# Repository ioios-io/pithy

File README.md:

# The Pithy Range @ [ioios.io](https://ioios.io/products/pithy)

---
## The quickest way to add extra control to your Smart Home
 The Pithy range was conceived to fill the gap in the smart home arena so as to provide simple and intuitive phyiscal controls for adjusting volume, dimming lights, changing heating settings or whatever you chose!

The Open-Source devices are centered around a Wemos D1 Mini and they all feature a rotary encoder, a side switch and a temperature/huimdity sensor. Additionally, the Pixel model has a 16 LED NeoPixel ring for a display whilst the Screen model has... you guessed it, a screen.

## Pins
When writing esphome configuration for the Pithy range you will need to use the following pins for the latest board versions.

| Function         | D1 Mini PIN |
|------------------|-------------|
| I2C Clock        | D3          |
| I2C Data         | D4          |
| Side Button      | TX          |
| PIR Sensor 1*    | D1          |
| PIR Sensor 2*    | D2          |
| Rotary Encoder A | D5          |
| Rotary Encoder B | D6          |
| Rotary Switch    | D7          |
| NeoPixels*       | RX          |
| DHT22 Temp*      | D0          |

(* Denotes items that may not be installed on all versions of a given model)

## The Files
In this repo you will find both the PCB files and the cases. In both sections the files are provided in multiple formats and include the official designs and also community contributions.
##### The Design Process
The PCBs were designed in Autodesk Eagle (using a custom made component library with 100% 3D renders). They were then imported/linked to Autodesk Fusion 360 where the cases were designed to perfectly fit and compliemnt the PCBs.

## Contributions
It is Open-Source for a reason! If you would like to contribute your modifications or creations to the project, please follow these steps:
1. Fork this repo
2. Create a new, descriptively-named directory within the appropriate 'community' directory
3. Create a README.md file to briefly explain your ideas and if required, instructions for use/assembly
4. Don't forget to credit yourself and anyone else involved!
4. Create a pull request

___

```
John Lumley
15th March 2021
```

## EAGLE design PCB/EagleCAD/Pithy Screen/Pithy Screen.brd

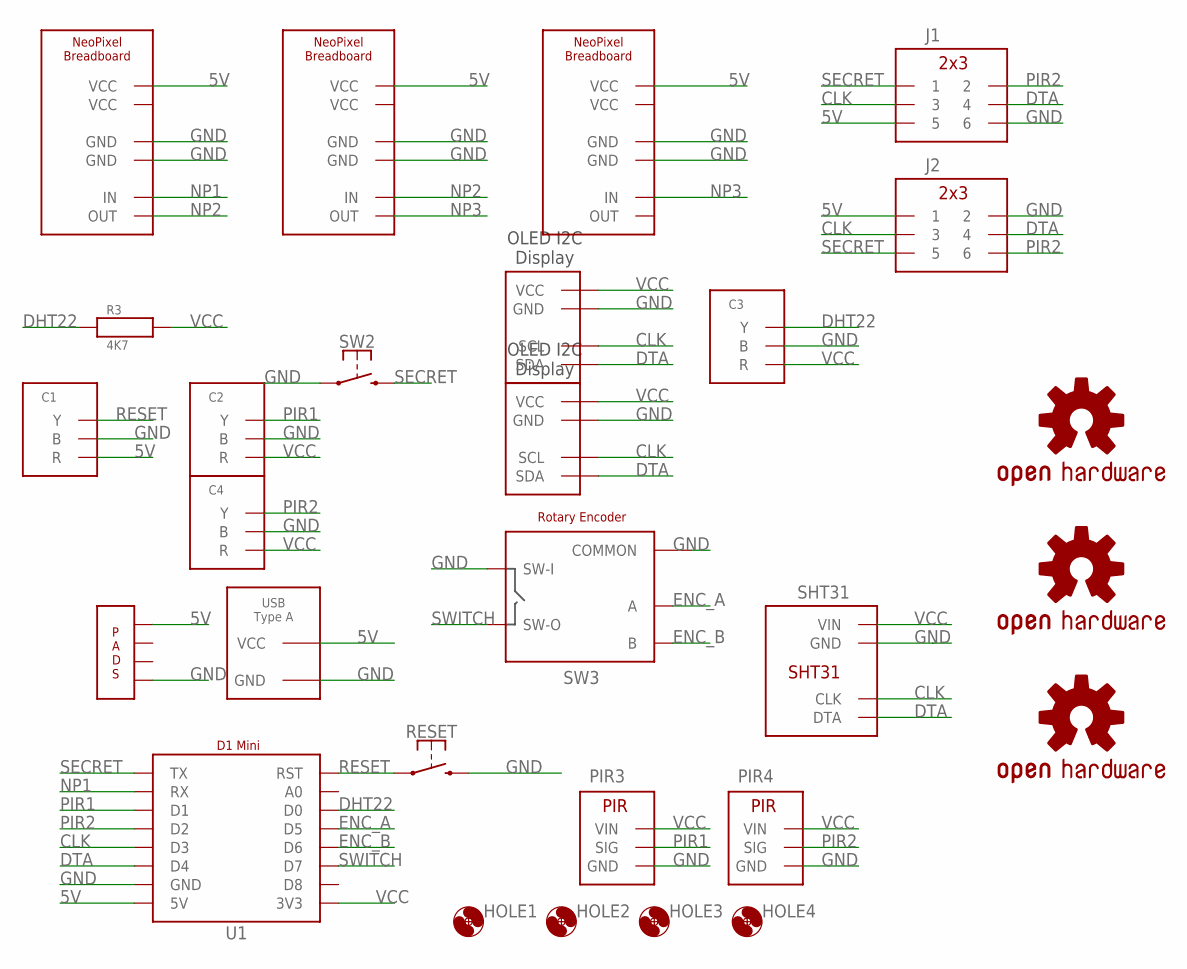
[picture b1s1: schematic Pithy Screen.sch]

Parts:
C1, C2, C3, C4: JST_2MM_3PIN
HOLE1, HOLE2, HOLE3, HOLE4: HOLE_3.2
J1, J2: DIL_2X03FEMALE; 2X3-RAF
LOGO1: OSHW-LOGOL; OSHW-LOGO-L
LOGO2: OSHW-LOGOM; OSHW-LOGO-M
LOGO3: OSHW-LOGOS; OSHW-LOGO-S
NP1, NP2, NP3: NEOPIXEL_BREADBOARD
PIR3, PIR4: PIR45DEG; PIR_45DEG
R3: 4K7; 1/4W_RESISTOR
RESET: SPDT_MOMENTARY; SPDT_RIGHT_ANGLE
SHT31: SHT31RIGHT_ANGLED; SHT31_RIGHT_ANGLE
SW2: SPDT_MOMENTARY; SPDT_RIGHT_ANGLE
SW3: ENCODER; ROTARY_ENCODER
U1: D1_MINI
U2, U3: OLED_I2C_0.9"VCC_LEFT; OLED_I2C_0.9"_ALT
U$1: USB_TYPE_A; USB_TYPE_A_BACKWARDS
U$2: PADS_4

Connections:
5V: C1.RED (R), J1.5, J2.1, NP1.VCC, NP2.VCC, NP3.VCC, U1.5V, U$1.VCC, U$2.P$4
CLK: J1.3, J2.3, SHT31.CLK, U1.D3, U2.SCL, U3.SCL
DHT22: C3.YELLOW (Y), R3.P$1, U1.D0
DTA: J1.4, J2.4, SHT31.DTA, U1.D4, U2.SDA, U3.SDA
ENC_A: SW3.A, U1.D5
ENC_B: SW3.B, U1.D6
GND: C1.BLACK (B), C2.BLACK (B), C3.BLACK (B), C4.BLACK (B), J1.6, J2.2, NP1.GND, NP1.GND@2 (GND), NP2.GND, NP2.GND@2 (GND), NP3.GND, NP3.GND@2 (GND), PIR3.GND, PIR4.GND, RESET.2 (3), SHT31.GND, SW2.1, SW3.C (COMMON), SW3.SW+ (SW-I), U1.GND, U2.GND, U3.GND, U$1.GND, U$2.P$1
NP1: NP1.IN, U1.RX
NP2: NP1.OUT, NP2.IN
NP3: NP2.OUT, NP3.IN
PIR1: C2.YELLOW (Y), PIR3.SIG, U1.D1
PIR2: C4.YELLOW (Y), J1.2, J2.6, PIR4.SIG, U1.D2
RESET: C1.YELLOW (Y), RESET.1, U1.RST
SECRET: J1.1, J2.5, SW2.2 (3), U1.TX
SWITCH: SW3.SW- (SW-O), U1.D7
VCC: C2.RED (R), C3.RED (R), C4.RED (R), PIR3.VCC (VIN), PIR4.VCC (VIN), R3.P$2, SHT31.VIN, U1.3V3, U2.VCC, U3.VCC

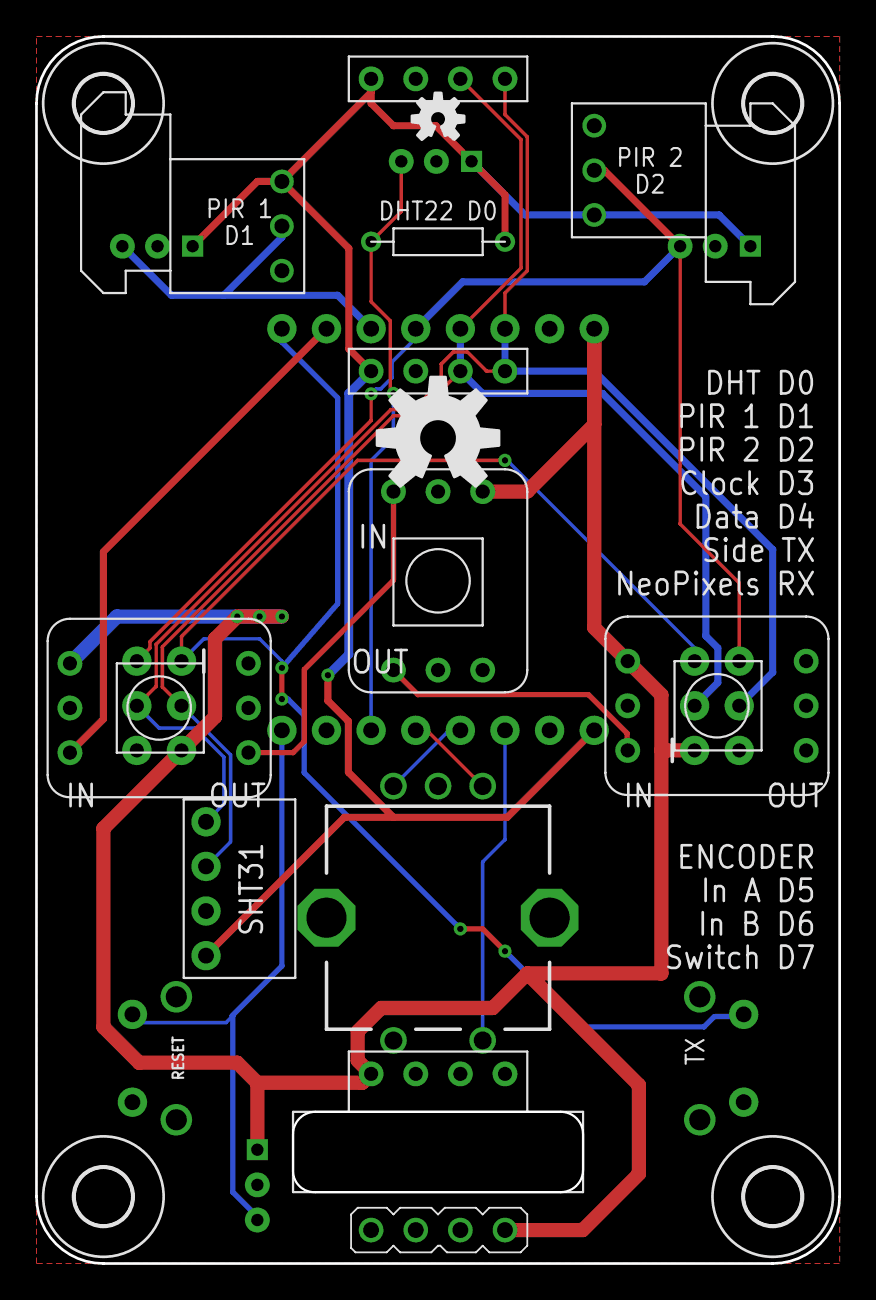
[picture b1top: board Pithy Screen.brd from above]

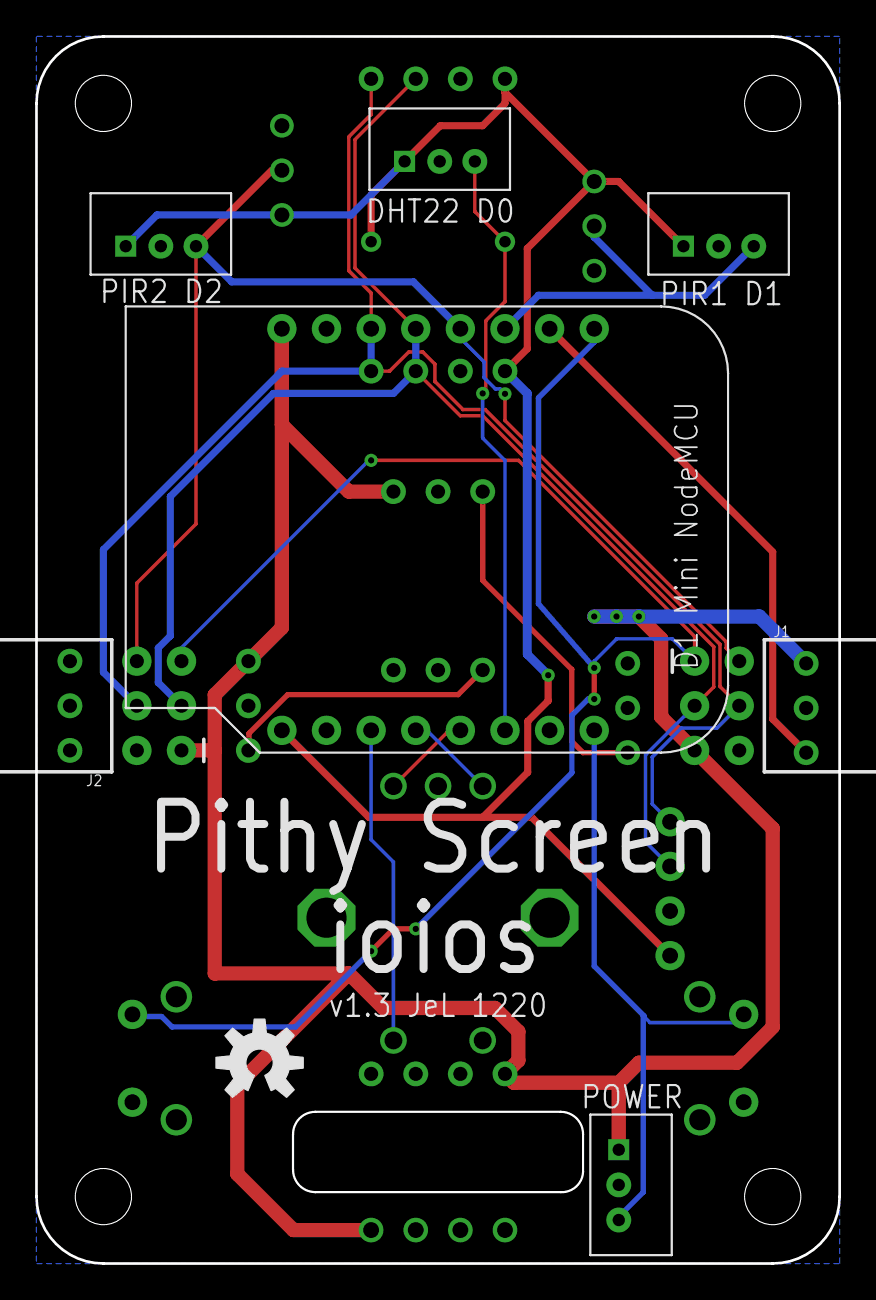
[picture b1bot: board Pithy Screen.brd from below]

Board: 2 copper layers, 45.7 x 69.8 mm, 28 parts (8 on the bottom side), 16 nets.

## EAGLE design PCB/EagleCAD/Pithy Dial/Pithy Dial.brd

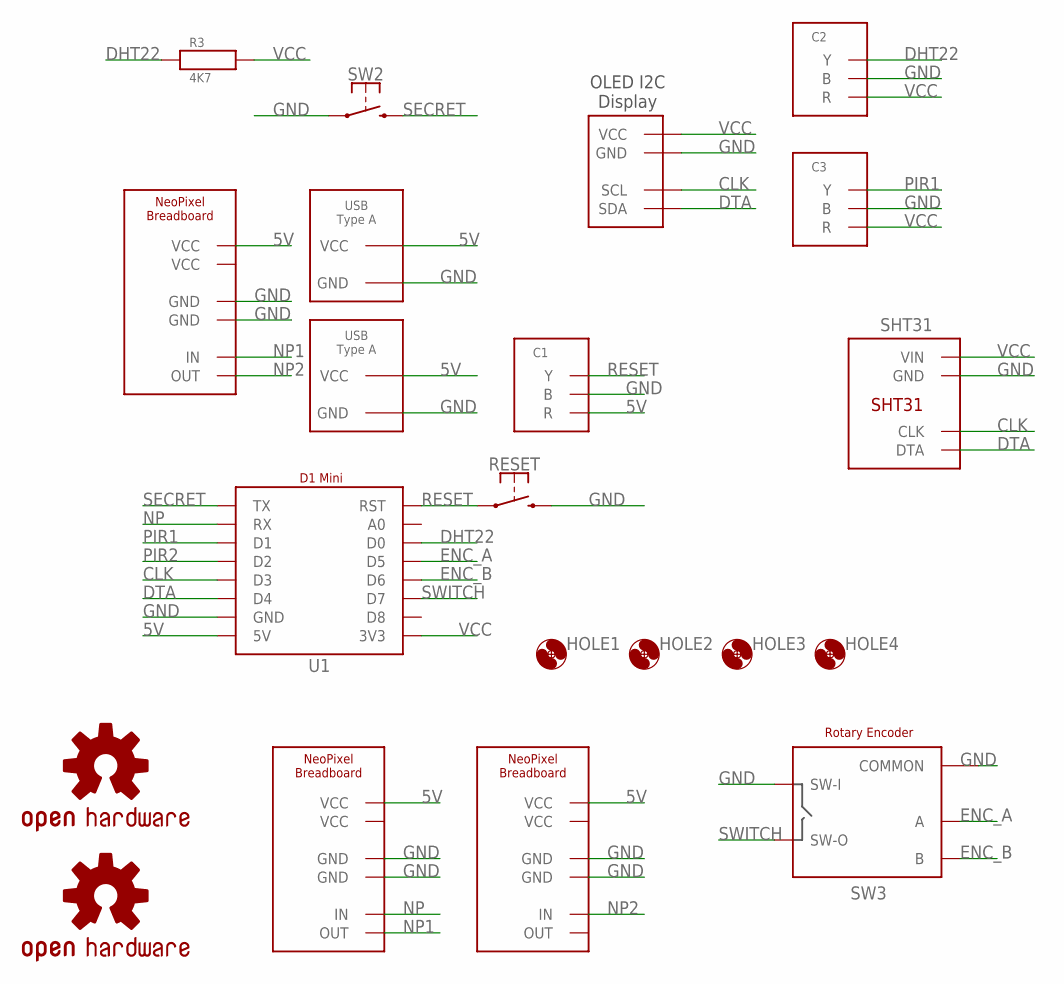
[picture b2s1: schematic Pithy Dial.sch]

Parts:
C1, C2, C3: JST_2MM_3PIN
HOLE1, HOLE2, HOLE3, HOLE4: HOLE_3.2
LOGO1: OSHW-LOGOM; OSHW-LOGO-M
LOGO2: OSHW-LOGOS; OSHW-LOGO-S
NP1: NEOPIXEL_BREADBOARD
NP2: LEFT_NEOPIXEL; NEOPIXEL_BREADBOARD
NP3: RIGHT_NEOPIXEL; NEOPIXEL_BREADBOARD
R3: 4K7; 1/4W_RESISTOR
RESET: SPDT_MOMENTARY; SPDT_RIGHT_ANGLE
SHT31: SHT31RIGHT_ANGLED; SHT31_RIGHT_ANGLE
SW2: SPDT_MOMENTARY; SPDT_RIGHT_ANGLE
SW3: ENCODER; ROTARY_ENCODER
U1: D1_MINI
U2: OLED_I2C_0.9"VCC_LEFT; OLED_I2C_0.9"_ALT
U$1, U$3: USB_TYPE_A; USB_TYPE_A_BACKWARDS

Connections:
5V: C1.RED (R), NP1.VCC, NP2.VCC, NP3.VCC, U1.5V, U$1.VCC, U$3.VCC
CLK: SHT31.CLK, U1.D3, U2.SCL
DHT22: C2.YELLOW (Y), R3.P$1, U1.D0
DTA: SHT31.DTA, U1.D4, U2.SDA
ENC_A: SW3.A, U1.D5
ENC_B: SW3.B, U1.D6
GND: C1.BLACK (B), C2.BLACK (B), C3.BLACK (B), NP1.GND, NP1.GND@2 (GND), NP2.GND, NP2.GND@2 (GND), NP3.GND, NP3.GND@2 (GND), RESET.2 (3), SHT31.GND, SW2.1, SW3.C (COMMON), SW3.SW+ (SW-I), U1.GND, U2.GND, U$1.GND, U$3.GND
NP: NP2.IN, U1.RX
NP1: NP1.IN, NP2.OUT
NP2: NP1.OUT, NP3.IN
PIR1: C3.YELLOW (Y), U1.D1
PIR2: U1.D2
RESET: C1.YELLOW (Y), RESET.1, U1.RST
SECRET: SW2.2 (3), U1.TX
SWITCH: SW3.SW- (SW-O), U1.D7
VCC: C2.RED (R), C3.RED (R), R3.P$2, SHT31.VIN, U1.3V3, U2.VCC

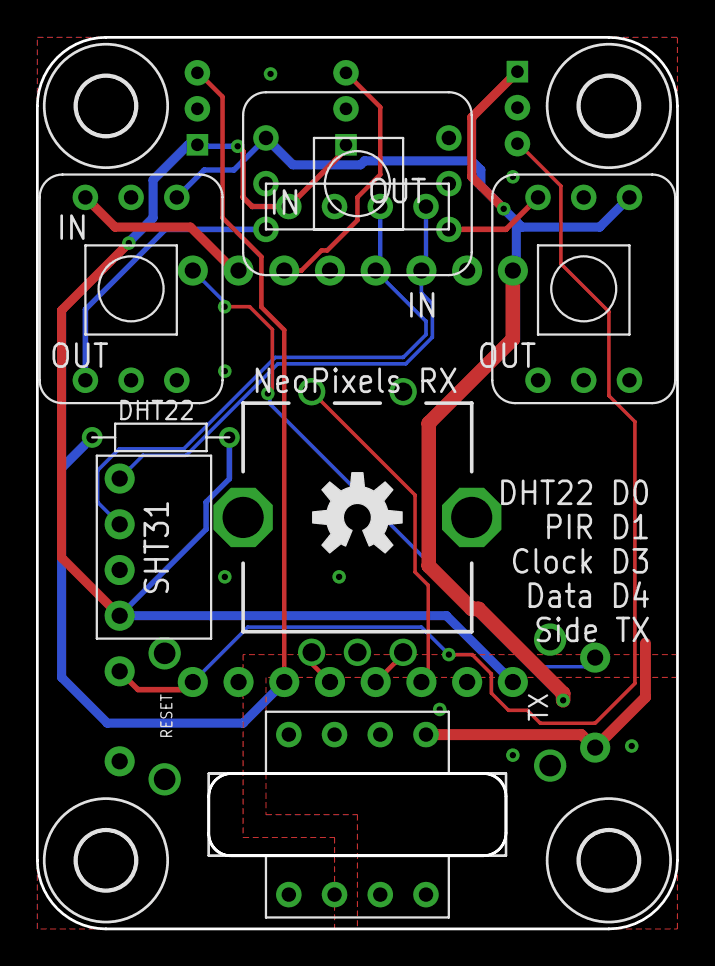
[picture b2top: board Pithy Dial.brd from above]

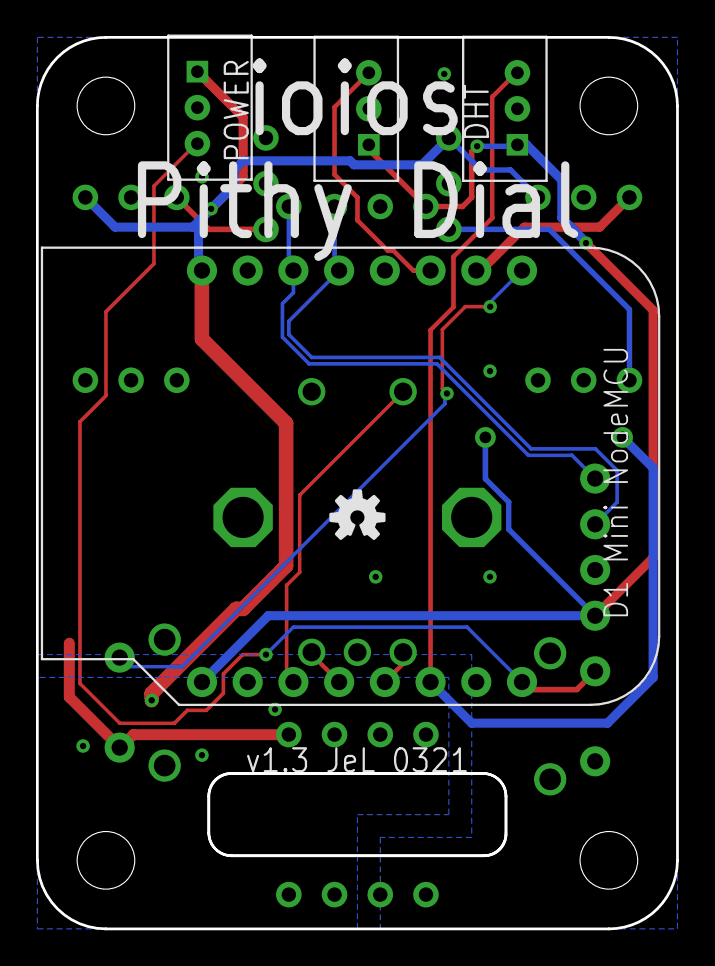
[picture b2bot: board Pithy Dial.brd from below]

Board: 2 copper layers, 35.6 x 49.5 mm, 21 parts (5 on the bottom side), 15 nets.

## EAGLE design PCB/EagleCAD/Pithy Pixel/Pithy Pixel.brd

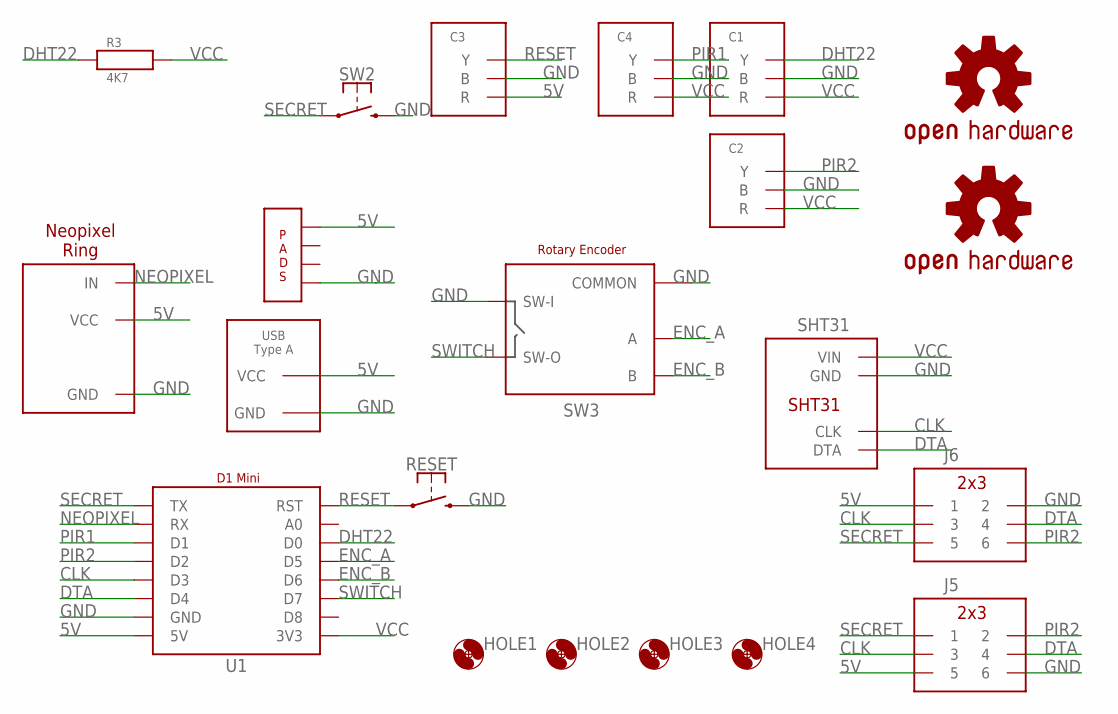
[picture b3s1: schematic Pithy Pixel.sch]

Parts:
C1, C2, C3, C4: JST_2MM_3PIN
HOLE1, HOLE2, HOLE3, HOLE4: HOLE_3.2
IC1: NEOPIXEL_RING_NO_OUT; NEOPIXEL_RING_SMALL_NO_OUT
J5, J6: DIL_2X03FEMALE; 2X3-RAF
LOGO1: OSHW-LOGOM; OSHW-LOGO-M
LOGO2: OSHW-LOGOS; OSHW-LOGO-S
R3: 4K7; 1/4W_RESISTOR
RESET: SPDT_MOMENTARY; SPDT_RIGHT_ANGLE
SHT31: SHT31RIGHT_ANGLED; SHT31_RIGHT_ANGLE
SW2: SPDT_MOMENTARY; SPDT_RIGHT_ANGLE
SW3: ENCODER; ROTARY_ENCODER
U1: D1_MINI
U$1: USB_TYPE_A; USB_TYPE_A_BACKWARDS
U$2: PADS_4

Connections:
5V: C3.RED (R), IC1.VCC@1 (VCC), J5.5, J6.1, U1.5V, U$1.VCC, U$2.P$4
CLK: J5.3, J6.3, SHT31.CLK, U1.D3
DHT22: C1.YELLOW (Y), R3.P$1, U1.D0
DTA: J5.4, J6.4, SHT31.DTA, U1.D4
ENC_A: SW3.A, U1.D5
ENC_B: SW3.B, U1.D6
GND: C1.BLACK (B), C2.BLACK (B), C3.BLACK (B), C4.BLACK (B), IC1.GND@2 (GND), J5.6, J6.2, RESET.2 (3), SHT31.GND, SW2.2 (3), SW3.C (COMMON), SW3.SW+ (SW-I), U1.GND, U$1.GND, U$2.P$1
NEOPIXEL: IC1.IN, U1.RX
PIR1: C4.YELLOW (Y), U1.D1
PIR2: C2.YELLOW (Y), J5.2, J6.6, U1.D2
RESET: C3.YELLOW (Y), RESET.1, U1.RST
SECRET: J5.1, J6.5, SW2.1, U1.TX
SWITCH: SW3.SW- (SW-O), U1.D7
VCC: C1.RED (R), C2.RED (R), C4.RED (R), R3.P$2, SHT31.VIN, U1.3V3

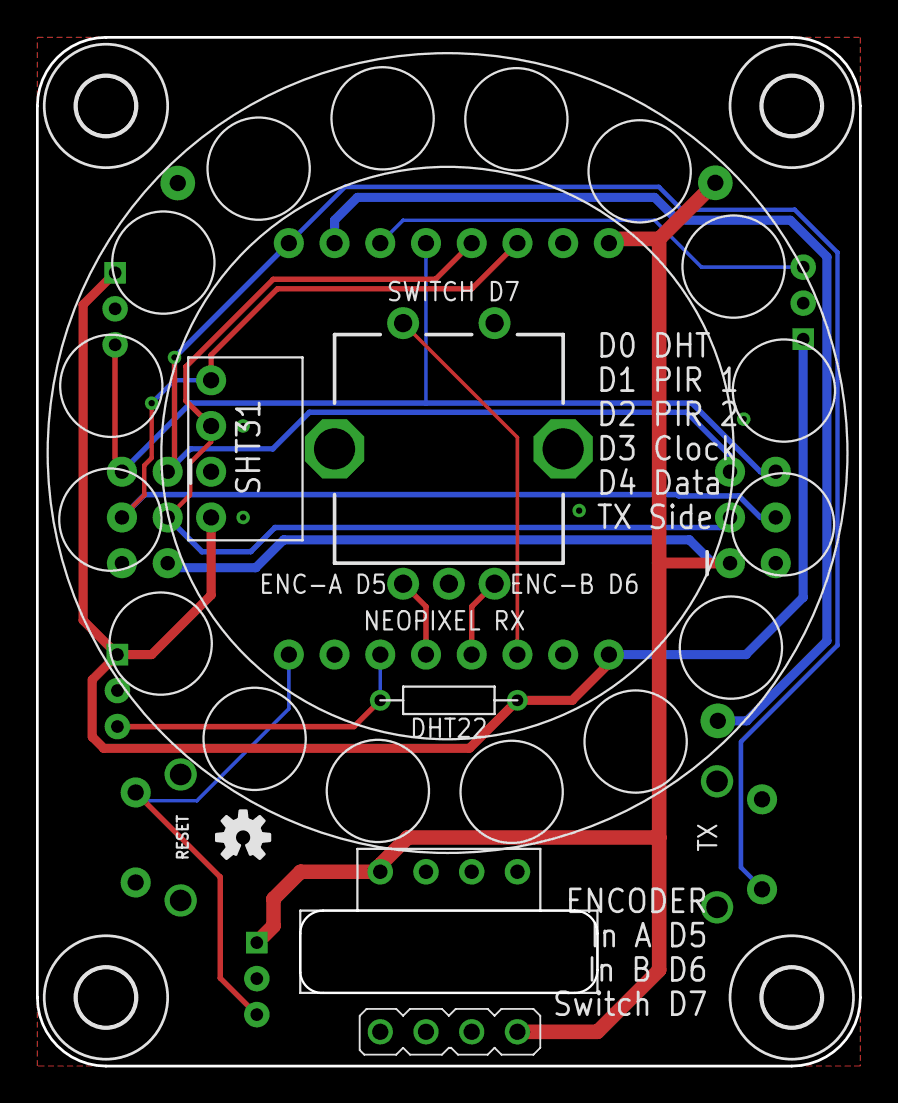
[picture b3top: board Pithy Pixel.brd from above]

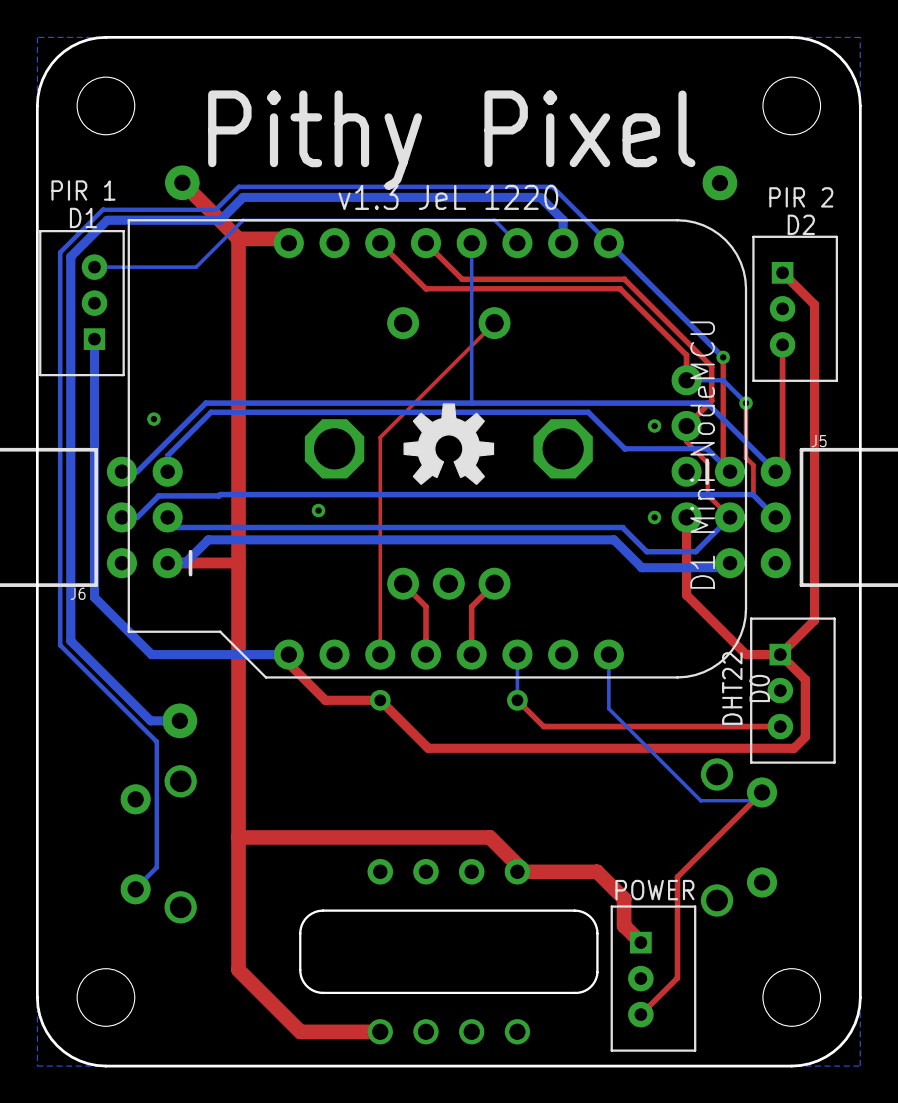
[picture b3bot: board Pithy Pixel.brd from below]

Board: 2 copper layers, 45.7 x 57.1 mm, 21 parts (8 on the bottom side), 14 nets.

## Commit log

2020-12-08 Added first STL files
2020-12-10 Banishing DS Store
2020-12-21 Adding Pithy Screen Plus range
2021-02-01 Screen and Screen Plus stp files
2021-02-05 Adding Screen STLs
2021-02-05 Adding Pixel STLs
2021-02-10 Screen Plus Faceplate updates
2021-03-18 Pithy Dial Plus basics
2021-03-18 Pithy Dialbasics
2021-03-18 Pithy Pixel Plus basics
2021-03-18 Added Wemos STL
2021-03-18 Thickening base
2021-03-18 Creating readme
2021-03-18 Misformatting MD readme
2021-03-18 Adding community structure
2021-03-18 move files to new community folder
2021-03-18 Readme tweak
2021-03-18 Directory & file rename
2021-03-28 Bulk upload of STLs
2021-03-28 Bulk upload of STEPs
2021-04-07 Adding mount options image
2021-06-05 Updating slanted stands
2021-06-09 Adding stls
2021-06-09 Adding steps
2021-06-19 Updating desk stands
2021-06-20 Adding PCB Files
2021-06-21 Adding Screen Straight Stand stl
2021-06-21 Adding Screen Straight Stand step
2021-07-03 Modifying straight stands
2021-07-11 Pithy Screen Updates
2021-10-08 Document the pin outs
    Partially addresses #3, adds a table documenting the pinouts for the D1 mini and which components they connect to.
